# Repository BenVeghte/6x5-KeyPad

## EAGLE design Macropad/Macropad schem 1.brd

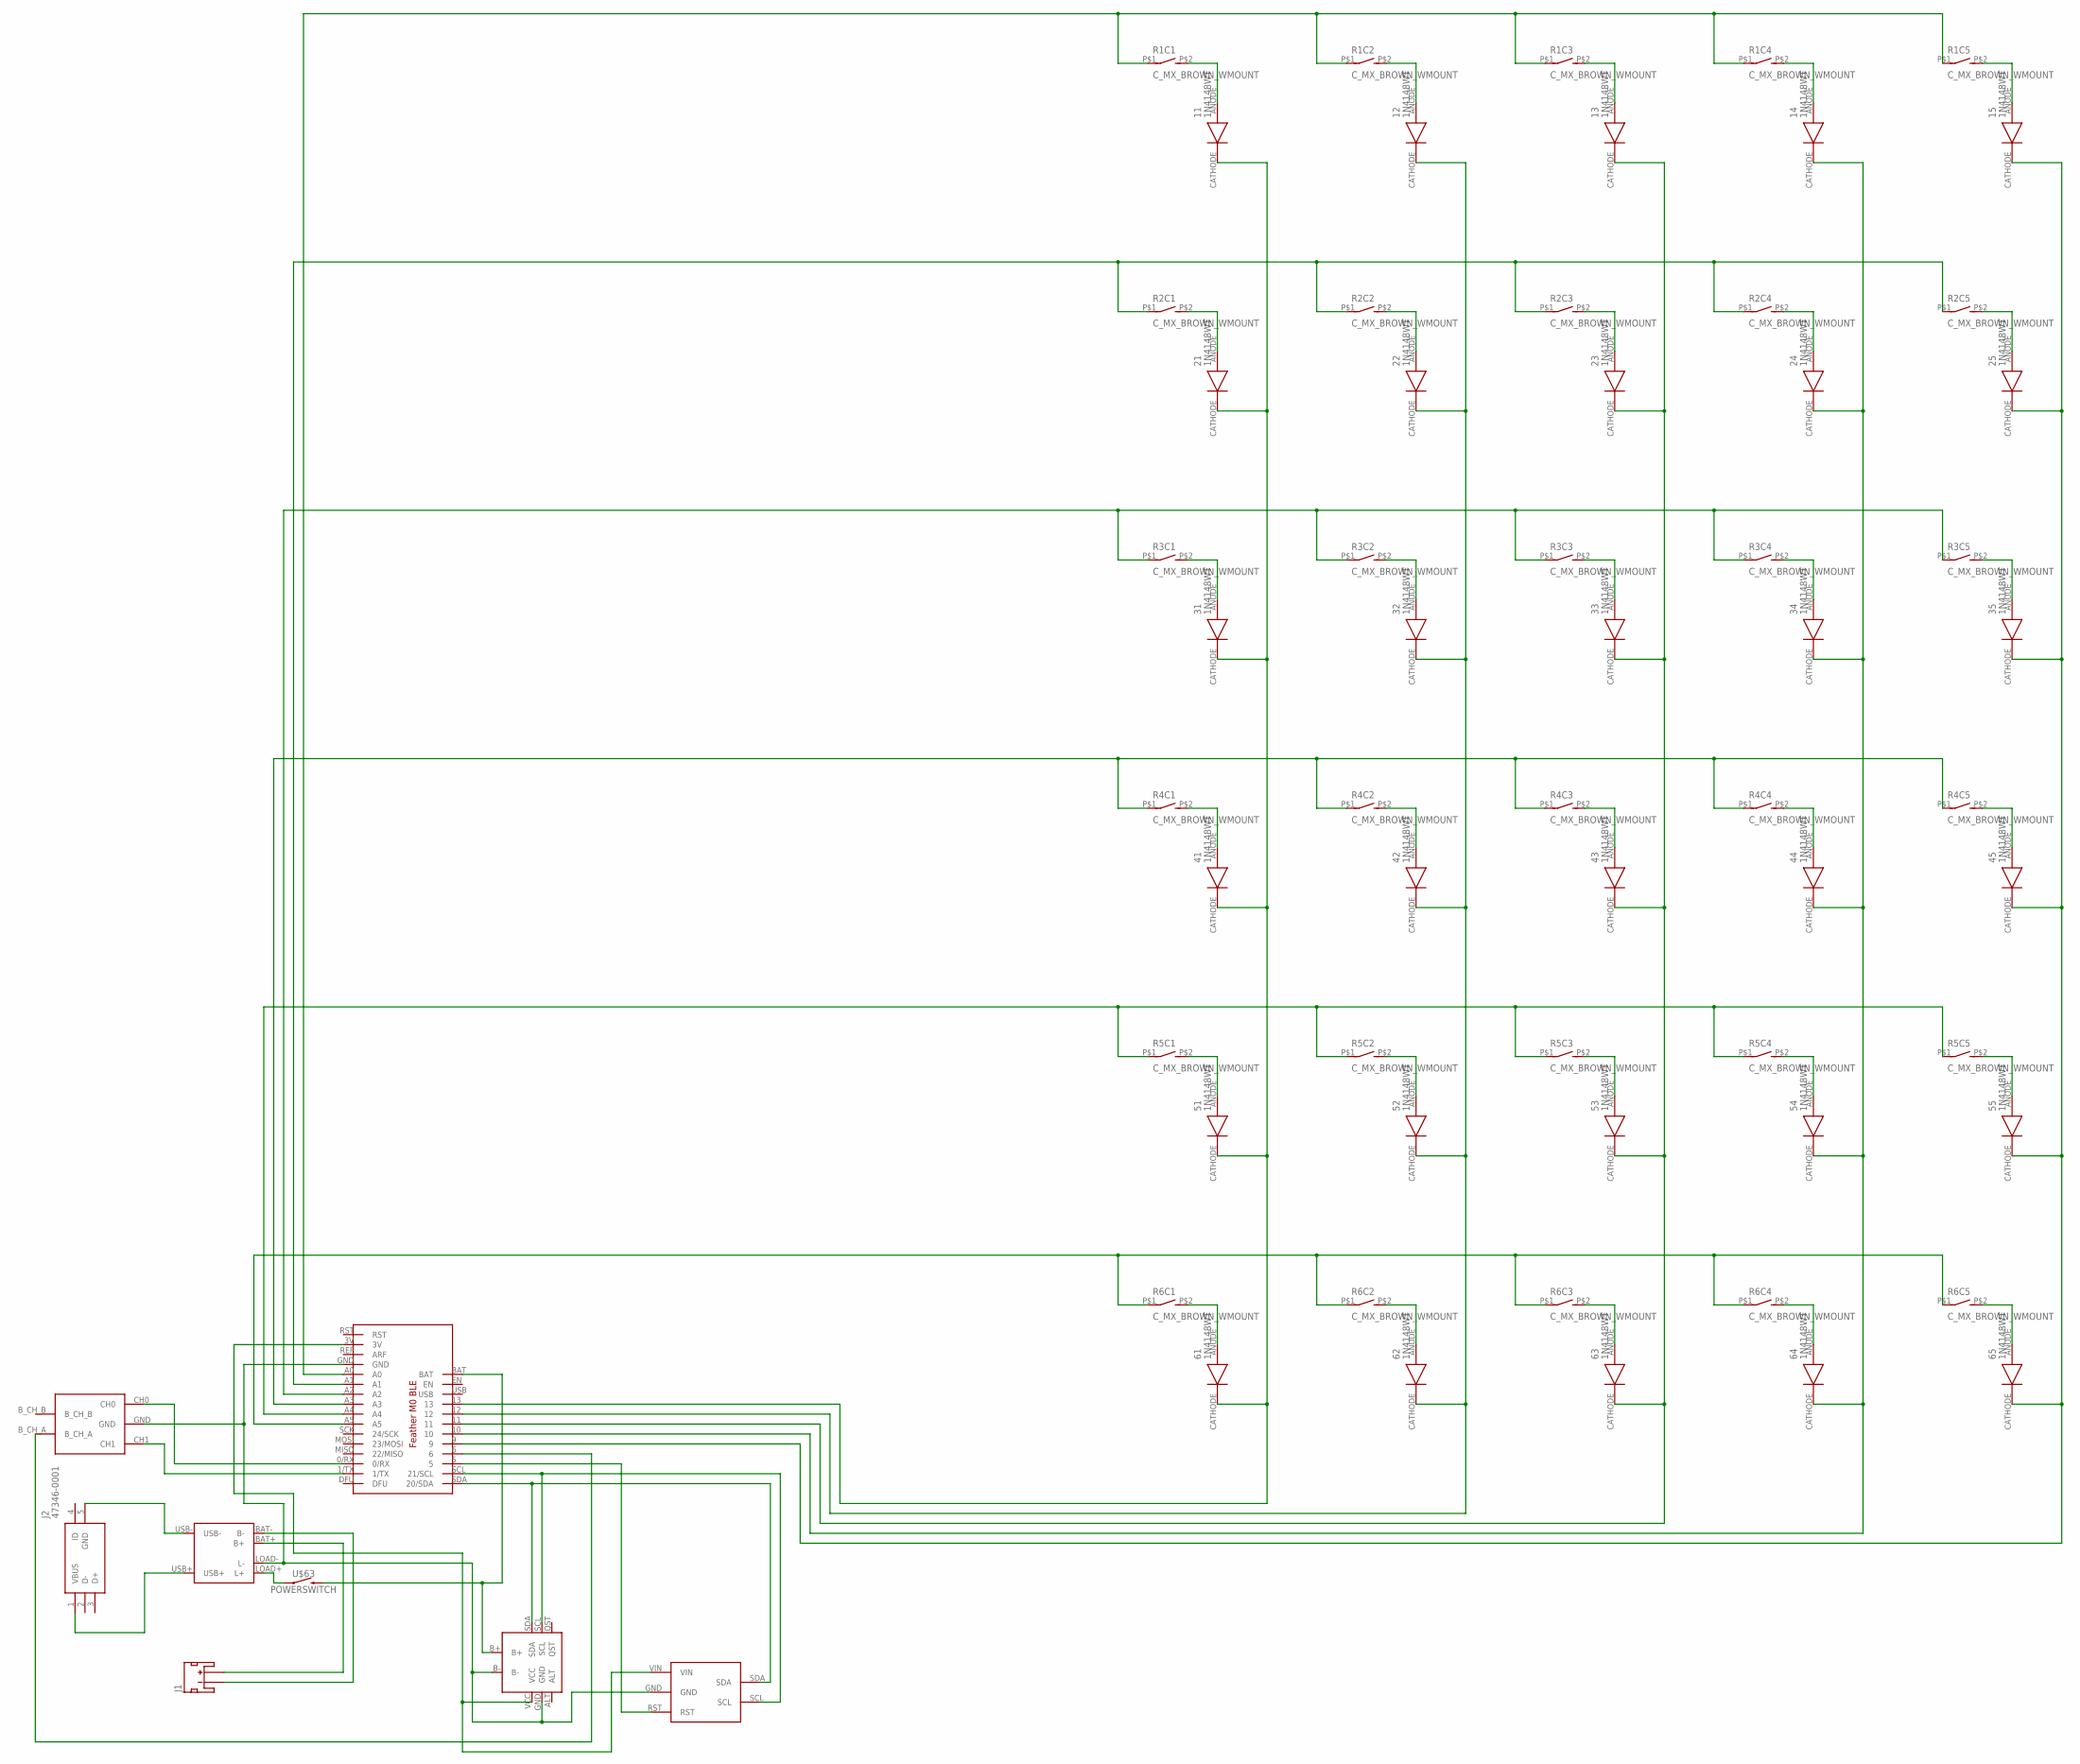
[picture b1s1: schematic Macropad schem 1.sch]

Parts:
11, 12, 13, 14, 15, 21, 22, 23, 24, 25, 31, 32, 33, 34, 35, 41, 42, 43, 44, 45, 51, 52, 53, 54, 55, 61, 62, 63, 64, 65: 1N4148WT
J1: JST_2MM_MALE; JST-2-SMD
J2: 47346-0001
R1C1, R1C2, R1C3, R1C4, R1C5, R2C1, R2C2, R2C3, R2C4, R2C5, R3C1, R3C2, R3C3, R3C4, R3C5, R4C1, R4C2, R4C3, R4C4, R4C5, R5C1, R5C2, R5C3, R5C4, R5C5, R6C1, R6C2, R6C3, R6C4, R6C5: C_MX_BROWN_WMOUNT
U$61: ADA_FEATHER_M0_BLE
U$62: ADA_LIIONCHARGER_V1.2
U$63: POWERSWITCH
U$64: LIPO_FUEL_GAUGE
U$65: COM-09117
U$66: I2C_OLED_DISP

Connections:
12: 12.CATHODE, 22.CATHODE, 32.CATHODE, 42.CATHODE, 52.CATHODE, 62.CATHODE, U$61.12
unnamed: 11.ANODE, R1C1.P$2 (2)
unnamed: 12.ANODE, R1C2.P$2 (2)
unnamed: 13.ANODE, R1C3.P$2 (2)
unnamed: 14.ANODE, R1C4.P$2 (2)
unnamed: 15.ANODE, R1C5.P$2 (2)
unnamed: R1C1.P$1 (1), R1C2.P$1 (1), R1C3.P$1 (1), R1C4.P$1 (1), R1C5.P$1 (1), U$61.A0
unnamed: 21.ANODE, R2C1.P$2 (2)
unnamed: 22.ANODE, R2C2.P$2 (2)
unnamed: 23.ANODE, R2C3.P$2 (2)
unnamed: 24.ANODE, R2C4.P$2 (2)
unnamed: 25.ANODE, R2C5.P$2 (2)
unnamed: R2C1.P$1 (1), R2C2.P$1 (1), R2C3.P$1 (1), R2C4.P$1 (1), R2C5.P$1 (1), U$61.A1
unnamed: 31.ANODE, R3C1.P$2 (2)
unnamed: 32.ANODE, R3C2.P$2 (2)
unnamed: 33.ANODE, R3C3.P$2 (2)
unnamed: 34.ANODE, R3C4.P$2 (2)
unnamed: 35.ANODE, R3C5.P$2 (2)
unnamed: R3C1.P$1 (1), R3C2.P$1 (1), R3C3.P$1 (1), R3C4.P$1 (1), R3C5.P$1 (1), U$61.A2
unnamed: 41.ANODE, R4C1.P$2 (2)
unnamed: 42.ANODE, R4C2.P$2 (2)
unnamed: 43.ANODE, R4C3.P$2 (2)
unnamed: 44.ANODE, R4C4.P$2 (2)
unnamed: 45.ANODE, R4C5.P$2 (2)
unnamed: R4C1.P$1 (1), R4C2.P$1 (1), R4C3.P$1 (1), R4C4.P$1 (1), R4C5.P$1 (1), U$61.A3
unnamed: 51.ANODE, R5C1.P$2 (2)
unnamed: 52.ANODE, R5C2.P$2 (2)
unnamed: 53.ANODE, R5C3.P$2 (2)
unnamed: 54.ANODE, R5C4.P$2 (2)
unnamed: 55.ANODE, R5C5.P$2 (2)
unnamed: R5C1.P$1 (1), R5C2.P$1 (1), R5C3.P$1 (1), R5C4.P$1 (1), R5C5.P$1 (1), U$61.A4
unnamed: 61.ANODE, R6C1.P$2 (2)
unnamed: 62.ANODE, R6C2.P$2 (2)
unnamed: 63.ANODE, R6C3.P$2 (2)
unnamed: 64.ANODE, R6C4.P$2 (2)
unnamed: 65.ANODE, R6C5.P$2 (2)
unnamed: R6C1.P$1 (1), R6C2.P$1 (1), R6C3.P$1 (1), R6C4.P$1 (1), R6C5.P$1 (1), U$61.A5
unnamed: 11.CATHODE, 21.CATHODE, 31.CATHODE, 41.CATHODE, 51.CATHODE, 61.CATHODE, U$61.13
unnamed: 13.CATHODE, 23.CATHODE, 33.CATHODE, 43.CATHODE, 53.CATHODE, 63.CATHODE, U$61.11
unnamed: 14.CATHODE, 24.CATHODE, 34.CATHODE, 44.CATHODE, 54.CATHODE, 64.CATHODE, U$61.10
unnamed: 15.CATHODE, 25.CATHODE, 35.CATHODE, 45.CATHODE, 55.CATHODE, 65.CATHODE, U$61.9
unnamed: U$62.LOAD+ (L+), U$63.1
unnamed: U$61.BAT, U$63.2, U$64.B+
unnamed: U$61.GND, U$62.LOAD- (L-), U$64.B-, U$64.GND, U$65.GND, U$66.GND
unnamed: U$61.SDA (20/SDA), U$64.SDA, U$66.SDA
unnamed: U$61.SCL (21/SCL), U$64.SCL, U$66.SCL
unnamed: J1.2 (+), U$62.BAT+ (B+)
unnamed: U$61.3V, U$64.VCC, U$66.VIN
unnamed: J1.1 (-), U$62.BAT- (B-)
unnamed: J2.5 (GND), U$62.USB-
unnamed: J2.1 (VBUS), U$62.USB+
unnamed: U$61.1/TX, U$65.CH1
unnamed: U$61.0/RX, U$65.CH0
unnamed: U$61.6, U$65.B_CH_A
unnamed: U$61.5, U$66.RST

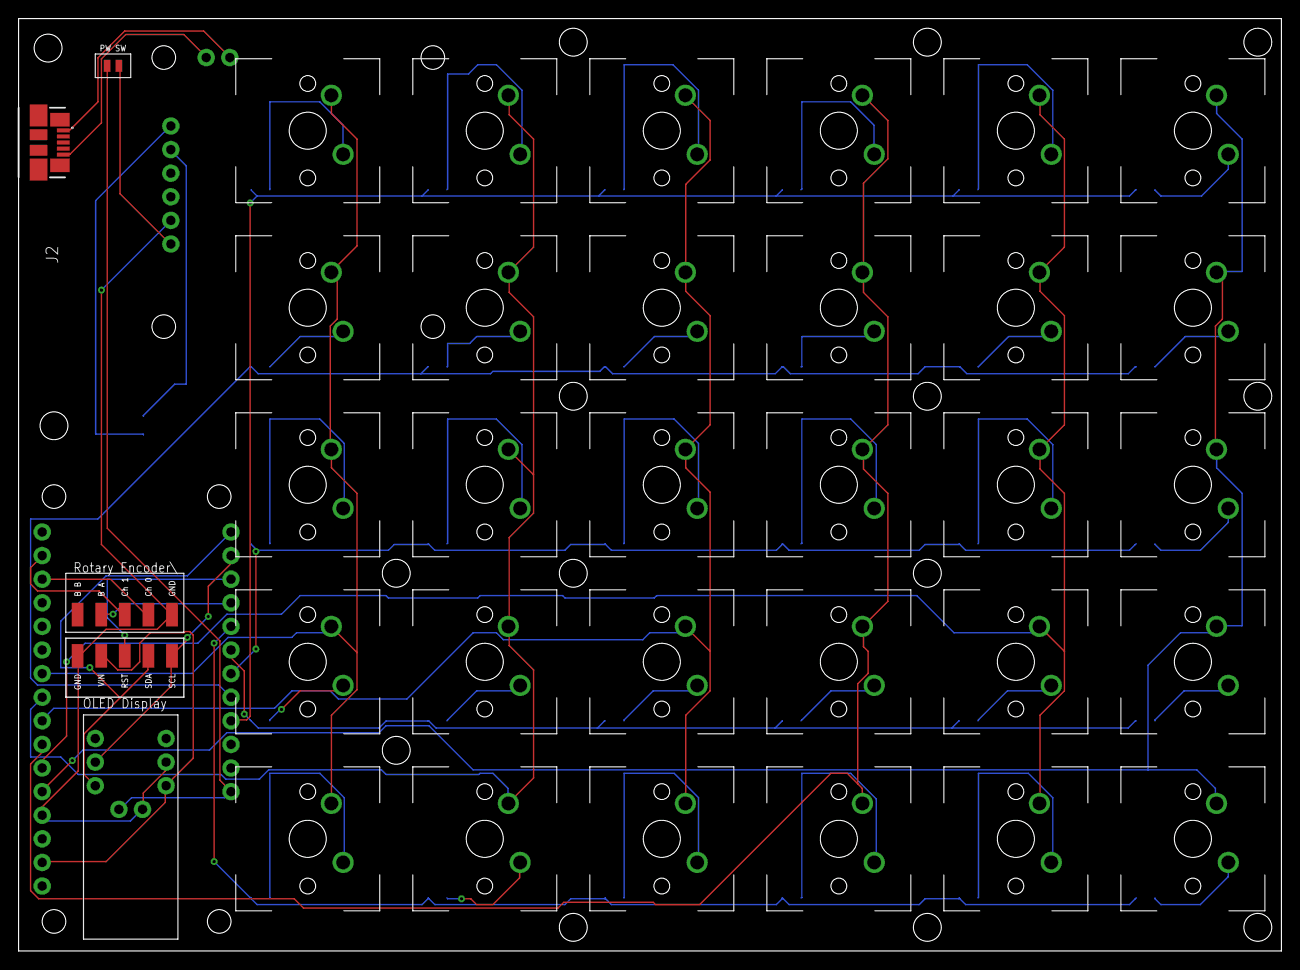
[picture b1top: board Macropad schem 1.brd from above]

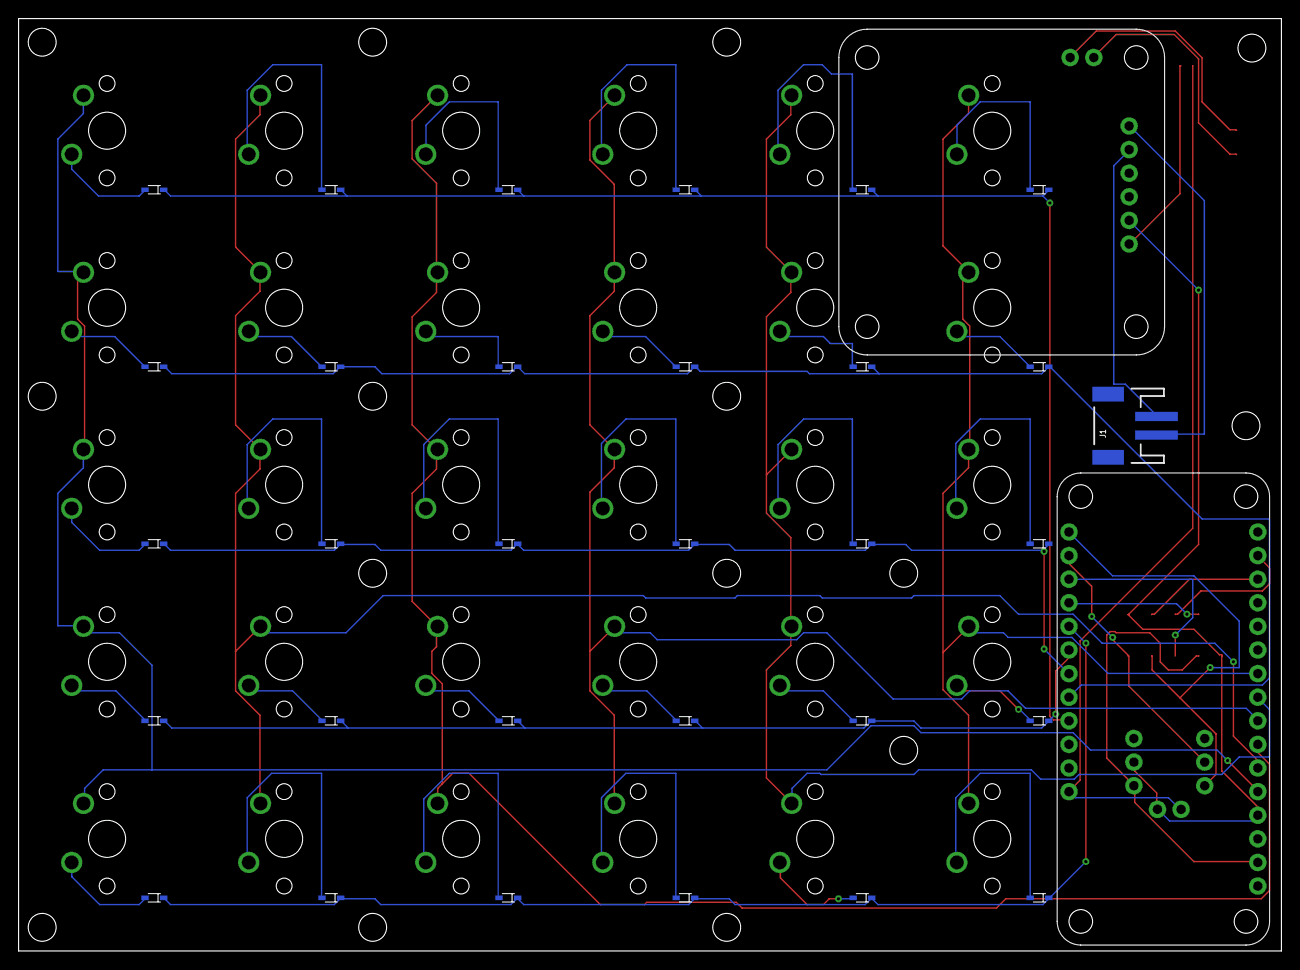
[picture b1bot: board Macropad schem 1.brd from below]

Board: 2 copper layers, 135.9 x 100.3 mm, 68 parts (33 on the bottom side), 55 nets.

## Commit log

2020-05-09 Add board and schematic files

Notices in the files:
parts and their libraries:
SparkFun-Connectors: Licensing: Creative Commons ShareAlike 4.0 International - https://creativecommons.org/licenses/by-sa/4.0
